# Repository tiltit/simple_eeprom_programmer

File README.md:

### Simple eeprom programmer

Simple programmer slapped together to write to 28Cxxx eeproms for a Z80 project.

Still needs improvements, mainly support for software write protect as mentioned in the 28Cxxx datasheet.

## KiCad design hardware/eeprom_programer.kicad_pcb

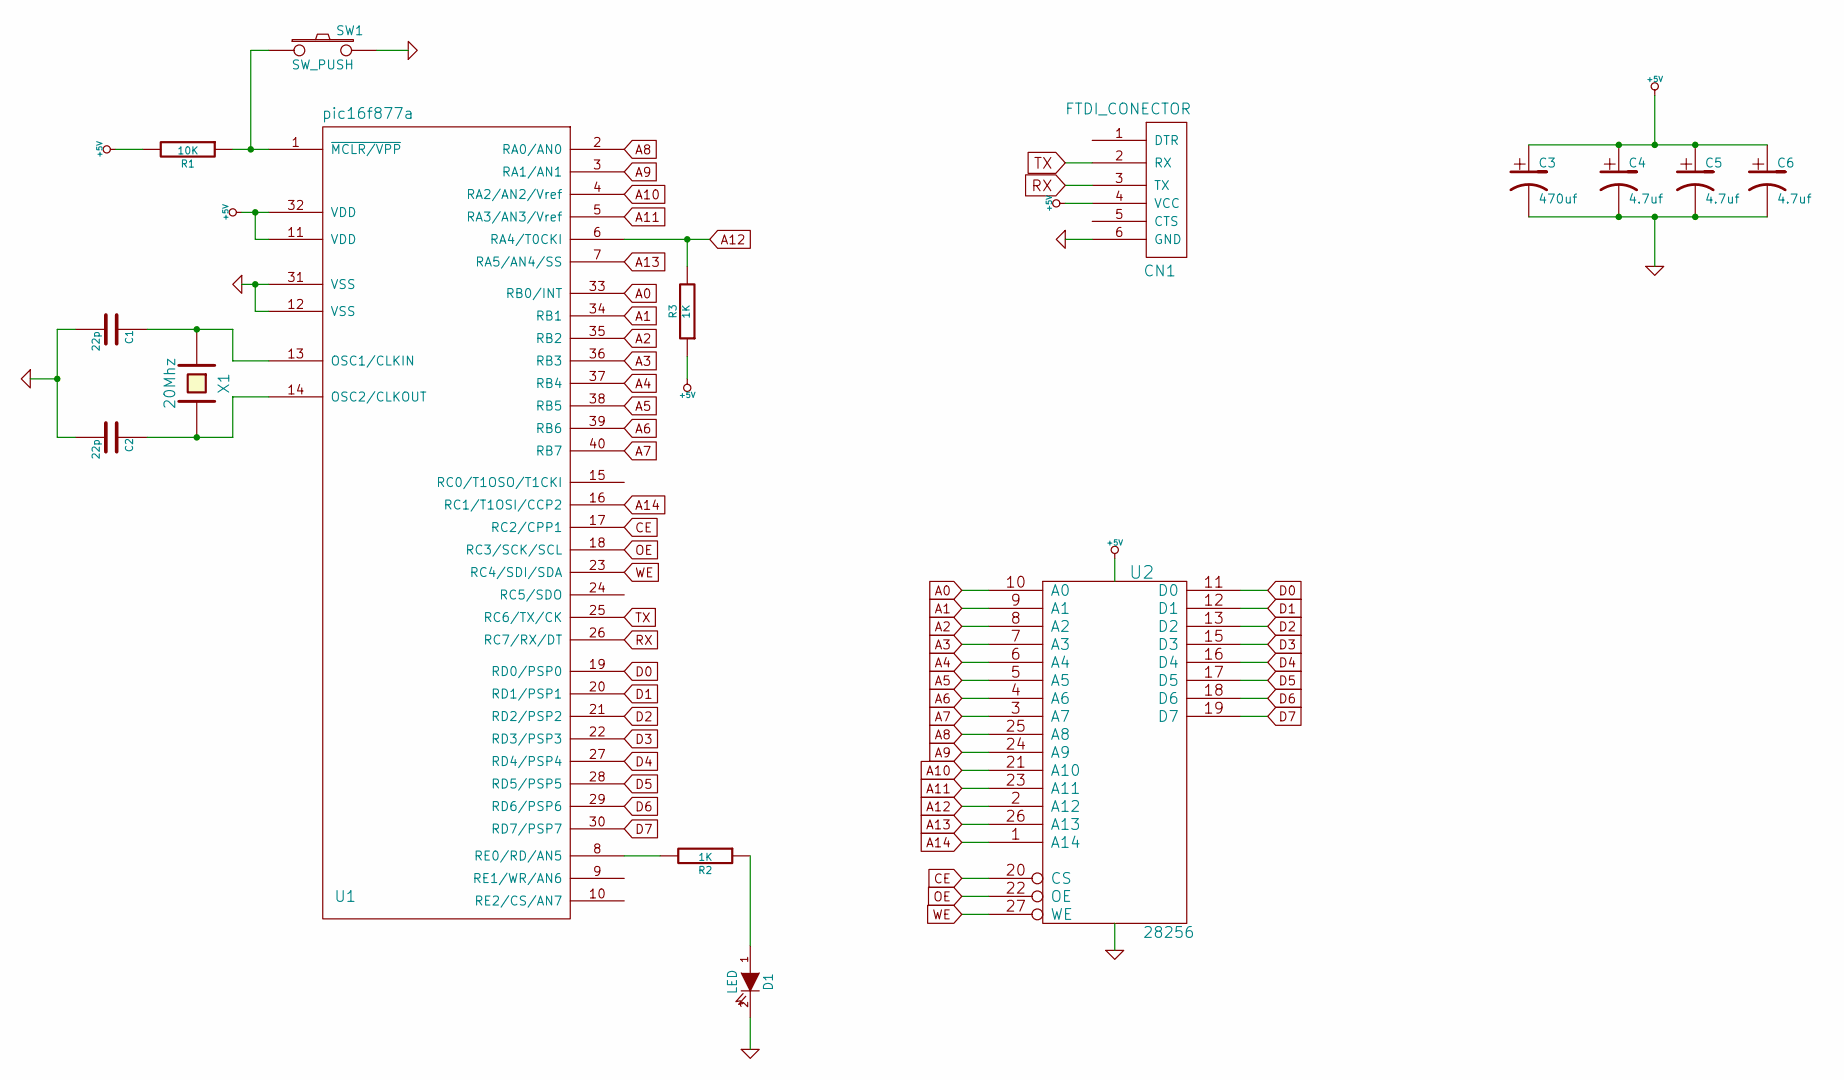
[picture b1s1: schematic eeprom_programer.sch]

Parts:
C1, C2: 22p; C2
C3: 470uf; Elko_vert_DM8_RM3-5
C4, C5, C6: 4.7uf; Elko_vert_DM5_RM2_CopperClear
CN1: FTDI_CONECTOR; Pin_Header_Straight_1x06
D1: LED; LED-3MM
R1: 10K; Resistor_Horizontal_RM10mm
R2, R3: 1K; Resistor_Horizontal_RM10mm
SW1: SW_PUSH; Puch_button_TH
U1: pic16f877a; DIP-40__600
U2: 28256; DIP-28__600
X1: 20Mhz; Crystal_HC50-U_Vertical

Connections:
+5V: C3.1, C4.1, C5.1, C6.1, CN1.4 (VCC), R1.2, R3.1, U1.11 (VDD), U1.32 (VDD), U2.28 (VCC)
A0: U1.33 (RB0/INT), U2.10 (A0)
A1: U1.34 (RB1), U2.9 (A1)
A2: U1.35 (RB2), U2.8 (A2)
A3: U1.36 (RB3), U2.7 (A3)
A4: U1.37 (RB4), U2.6 (A4)
A5: U1.38 (RB5), U2.5 (A5)
A6: U1.39 (RB6), U2.4 (A6)
A7: U1.40 (RB7), U2.3 (A7)
A8: U1.2 (RA0/AN0), U2.25 (A8)
A9: U1.3 (RA1/AN1), U2.24 (A9)
A10: U1.4 (RA2/AN2/Vref), U2.21 (A10)
A11: U1.5 (RA3/AN3/Vref), U2.23 (A11)
A12: R3.2, U1.6 (RA4/T0CKI), U2.2 (A12)
A13: U1.7 (RA5/AN4/SS), U2.26 (A13)
A14: U1.16 (RC1/T1OSI/CCP2), U2.1 (A14)
CE: U1.17 (RC2/CPP1), U2.20 (CS)
D0: U1.19 (RD0/PSP0), U2.11 (D0)
D1: U1.20 (RD1/PSP1), U2.12 (D1)
D2: U1.21 (RD2/PSP2), U2.13 (D2)
D3: U1.22 (RD3/PSP3), U2.15 (D3)
D4: U1.27 (RD4/PSP4), U2.16 (D4)
D5: U1.28 (RD5/PSP5), U2.17 (D5)
D6: U1.29 (RD6/PSP6), U2.18 (D6)
D7: U1.30 (RD7/PSP7), U2.19 (D7)
GND: C1.2, C2.2, C3.2, C4.2, C5.2, C6.2, CN1.6 (GND), D1.2 (K), SW1.2, U1.12 (VSS), U1.31 (VSS), U2.14 (GND)
unnamed: C1.1, U1.13 (OSC1/CLKIN), X1.1
unnamed: C2.1, U1.14 (OSC2/CLKOUT), X1.2
unnamed: D1.1 (A), R2.1
unnamed: R1.1, SW1.1, U1.1 (~MCLR/VPP)
unnamed: R2.2, U1.8 (RE0/RD/AN5)
OE: U1.18 (RC3/SCK/SCL), U2.22 (OE)
RX: CN1.3 (TX), U1.26 (RC7/RX/DT)
TX: CN1.2 (RX), U1.25 (RC6/TX/CK)
WE: U1.23 (RC4/SDI/SDA), U2.27 (WE)

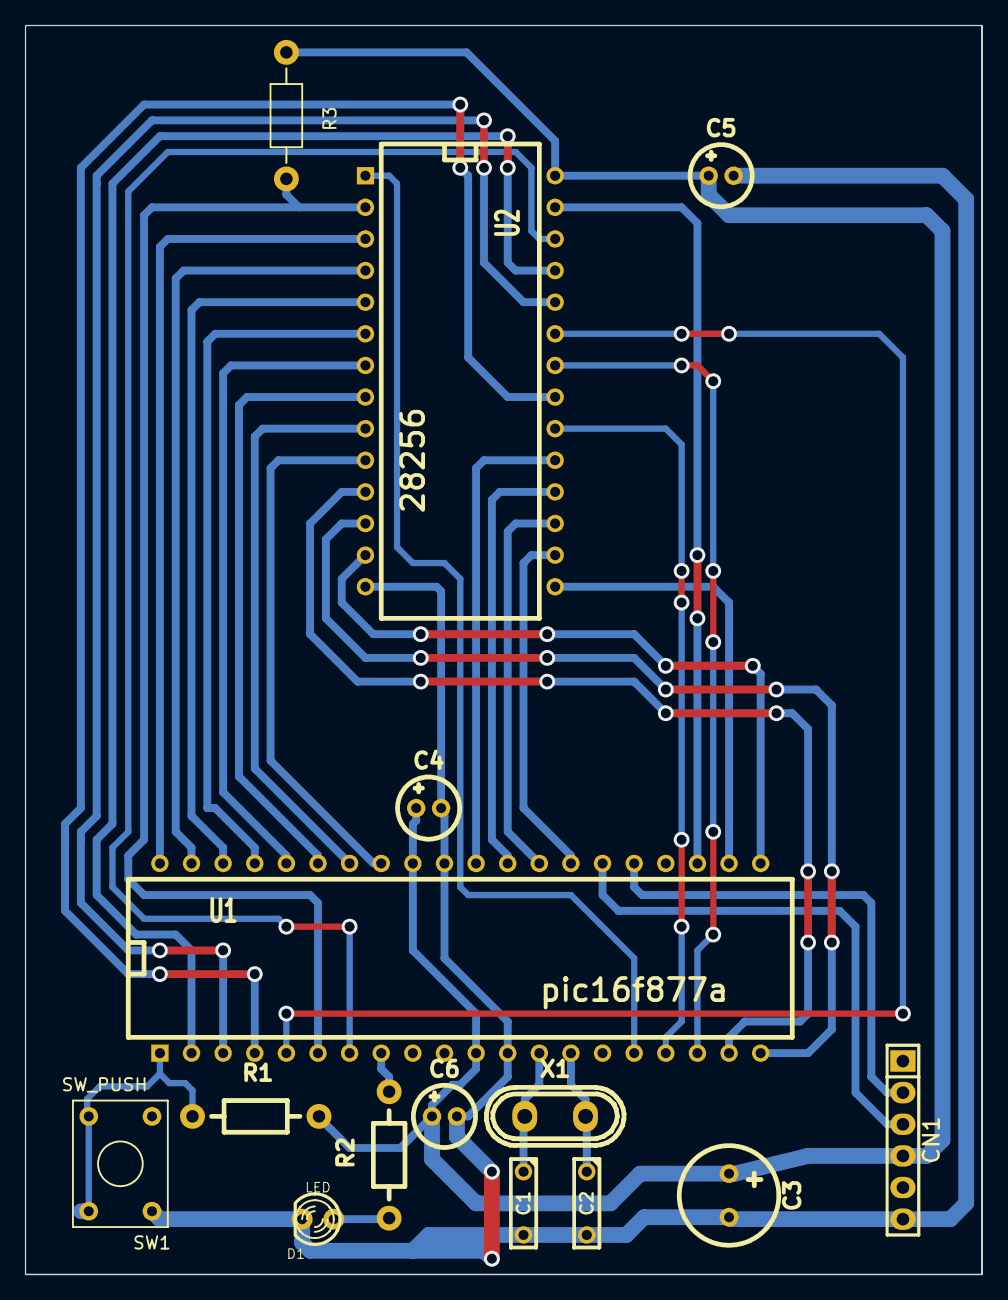
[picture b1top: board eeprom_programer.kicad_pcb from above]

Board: 2 copper layers, 76.8 x 100.3 mm, 15 parts (0 on the bottom side), 35 nets.
